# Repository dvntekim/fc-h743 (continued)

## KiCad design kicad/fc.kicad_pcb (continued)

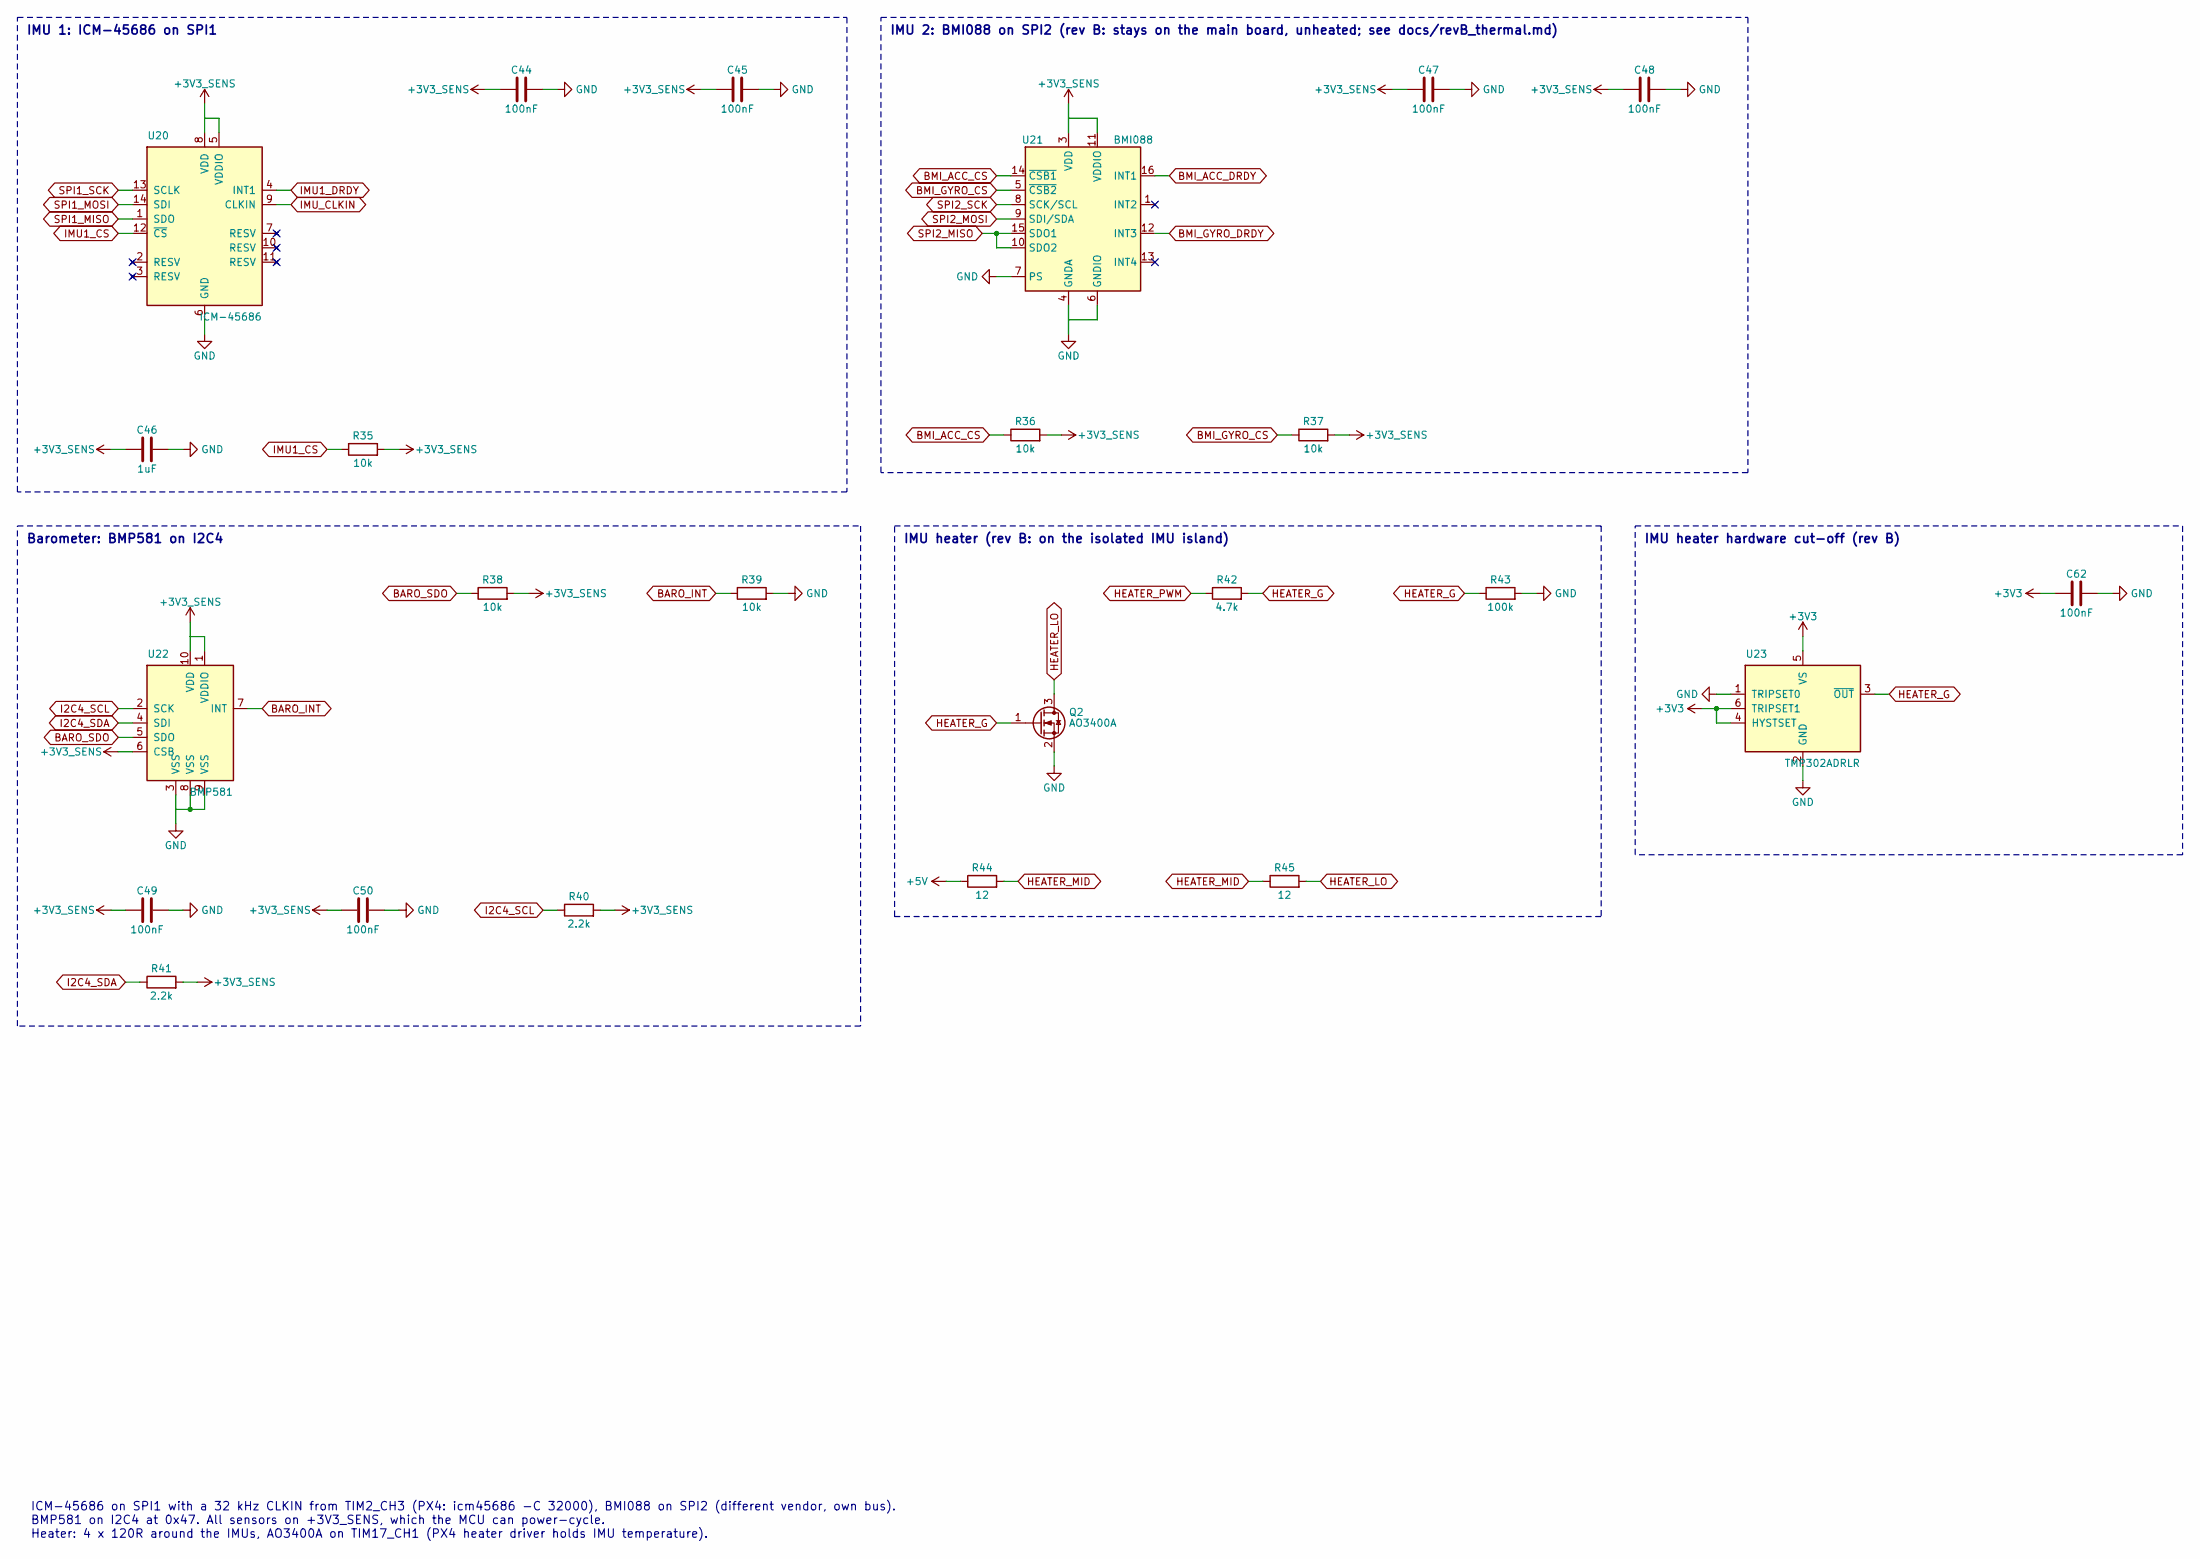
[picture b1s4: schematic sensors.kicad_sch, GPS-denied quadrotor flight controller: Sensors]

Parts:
C44, C45, C47, C48, C49, C50, C62: 100nF; C_0402_1005Metric; Rating 16V X7R; LCSC C1525
C46: 1uF; C_0402_1005Metric; Rating 25V X5R; LCSC C52923
Q2: AO3400A; SOT-23; LCSC C20917
R35, R36, R37, R38, R39: 10k; R_0402_1005Metric; LCSC C25744
R40, R41: 2.2k; R_0402_1005Metric; LCSC C25879
R42: 4.7k; R_0402_1005Metric; LCSC C25900
R43: 100k; R_0402_1005Metric; LCSC C25741
R44, R45: 12; R_2010_5025Metric; LCSC C3013299
U20: ICM-45686; LGA-14_3x2.5mm_P0.5mm_LayoutBorder3x4y; LCSC C22459454
U21: BMI088; Bosch_LGA-16_4.5x3mm_P0.5mm_LayoutBorder7x1y_ClockwisePinNu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; LCSC C194919
U22: BMP581; Bosch_LGA-10_2x2mm_P0.5mm_BMP581; LCSC C5362283
U23: TMP302ADRLR; SOT-563; LCSC C2877557

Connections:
+3V3: C62.1, U23.4 (HYSTSET), U23.5 (VS), U23.6 (TRIPSET1); also elsewhere on the board
+3V3_SENS: C44.1, C45.1, C46.1, C47.1, C48.1, C49.1, C50.1, R35.2, R36.2, R37.2, R38.2, R40.2, R41.2, U20.5 (VDDIO), U20.8 (VDD), U21.3 (VDD), U21.11 (VDDIO), U22.1 (VDDIO), U22.6 (CSB), U22.10 (VDD); also elsewhere on the board
+5V: R44.1; also elsewhere on the board
BARO_INT: R39.1, U22.7 (INT)
BARO_SDO: R38.1, U22.5 (SDO)
BMI_ACC_CS: R36.1, U21.14 (~CSB1); also elsewhere on the board
BMI_ACC_DRDY: U21.16 (INT1); also elsewhere on the board
BMI_GYRO_CS: R37.1, U21.5 (~CSB2); also elsewhere on the board
BMI_GYRO_DRDY: U21.12 (INT3); also elsewhere on the board
GND: C44.2, C45.2, C46.2, C47.2, C48.2, C49.2, C50.2, C62.2, Q2.2 (S), R39.2, R43.2, U20.6 (GND), U21.2 (GNDA), U21.4 (GNDA), U21.6 (GNDIO), U21.7 (PS), U22.3 (VSS), U22.8 (VSS), U22.9 (VSS), U23.1 (TRIPSET0), U23.2 (GND); also elsewhere on the board
HEATER_G: Q2.1 (G), R42.2, R43.1, U23.3 (~OUT)
HEATER_LO: Q2.3 (D), R45.2
HEATER_MID: R44.2, R45.1
HEATER_PWM: R42.1; also elsewhere on the board
I2C4_SCL: R40.1, U22.2 (SCK); also elsewhere on the board
I2C4_SDA: R41.1, U22.4 (SDI); also elsewhere on the board
IMU1_CS: R35.1, U20.12 (~CS); also elsewhere on the board
IMU1_DRDY: U20.4 (INT1); also elsewhere on the board
IMU_CLKIN: U20.9 (CLKIN); also elsewhere on the board
SPI1_MISO: U20.1 (SDO); also elsewhere on the board
SPI1_MOSI: U20.14 (SDI); also elsewhere on the board
SPI1_SCK: U20.13 (SCLK); also elsewhere on the board
SPI2_MISO: U21.10 (SDO2), U21.15 (SDO1); also elsewhere on the board
SPI2_MOSI: U21.9 (SDI/SDA); also elsewhere on the board
SPI2_SCK: U21.8 (SCK/SCL); also elsewhere on the board

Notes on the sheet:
IMU 1: ICM-45686 on SPI1
IMU 2: BMI088 on SPI2 (rev B: stays on the main board, unheated; see docs/revB_thermal.md)
Barometer: BMP581 on I2C4
IMU heater (rev B: on the isolated IMU island)
IMU heater hardware cut-off (rev B)
ICM-45686 on SPI1 with a 32 kHz CLKIN from TIM2_CH3 (PX4: icm45686 -C 32000), BMI088 on SPI2 (different vendor, own bus). BMP581 on I2C4 at 0x47. All sensors on +3V3_SENS, which the MCU can power-cycle. Heater: 4 x 120R around the IMUs, AO3400A on TIM17_CH1 (PX4 heater driver holds IMU temperature).

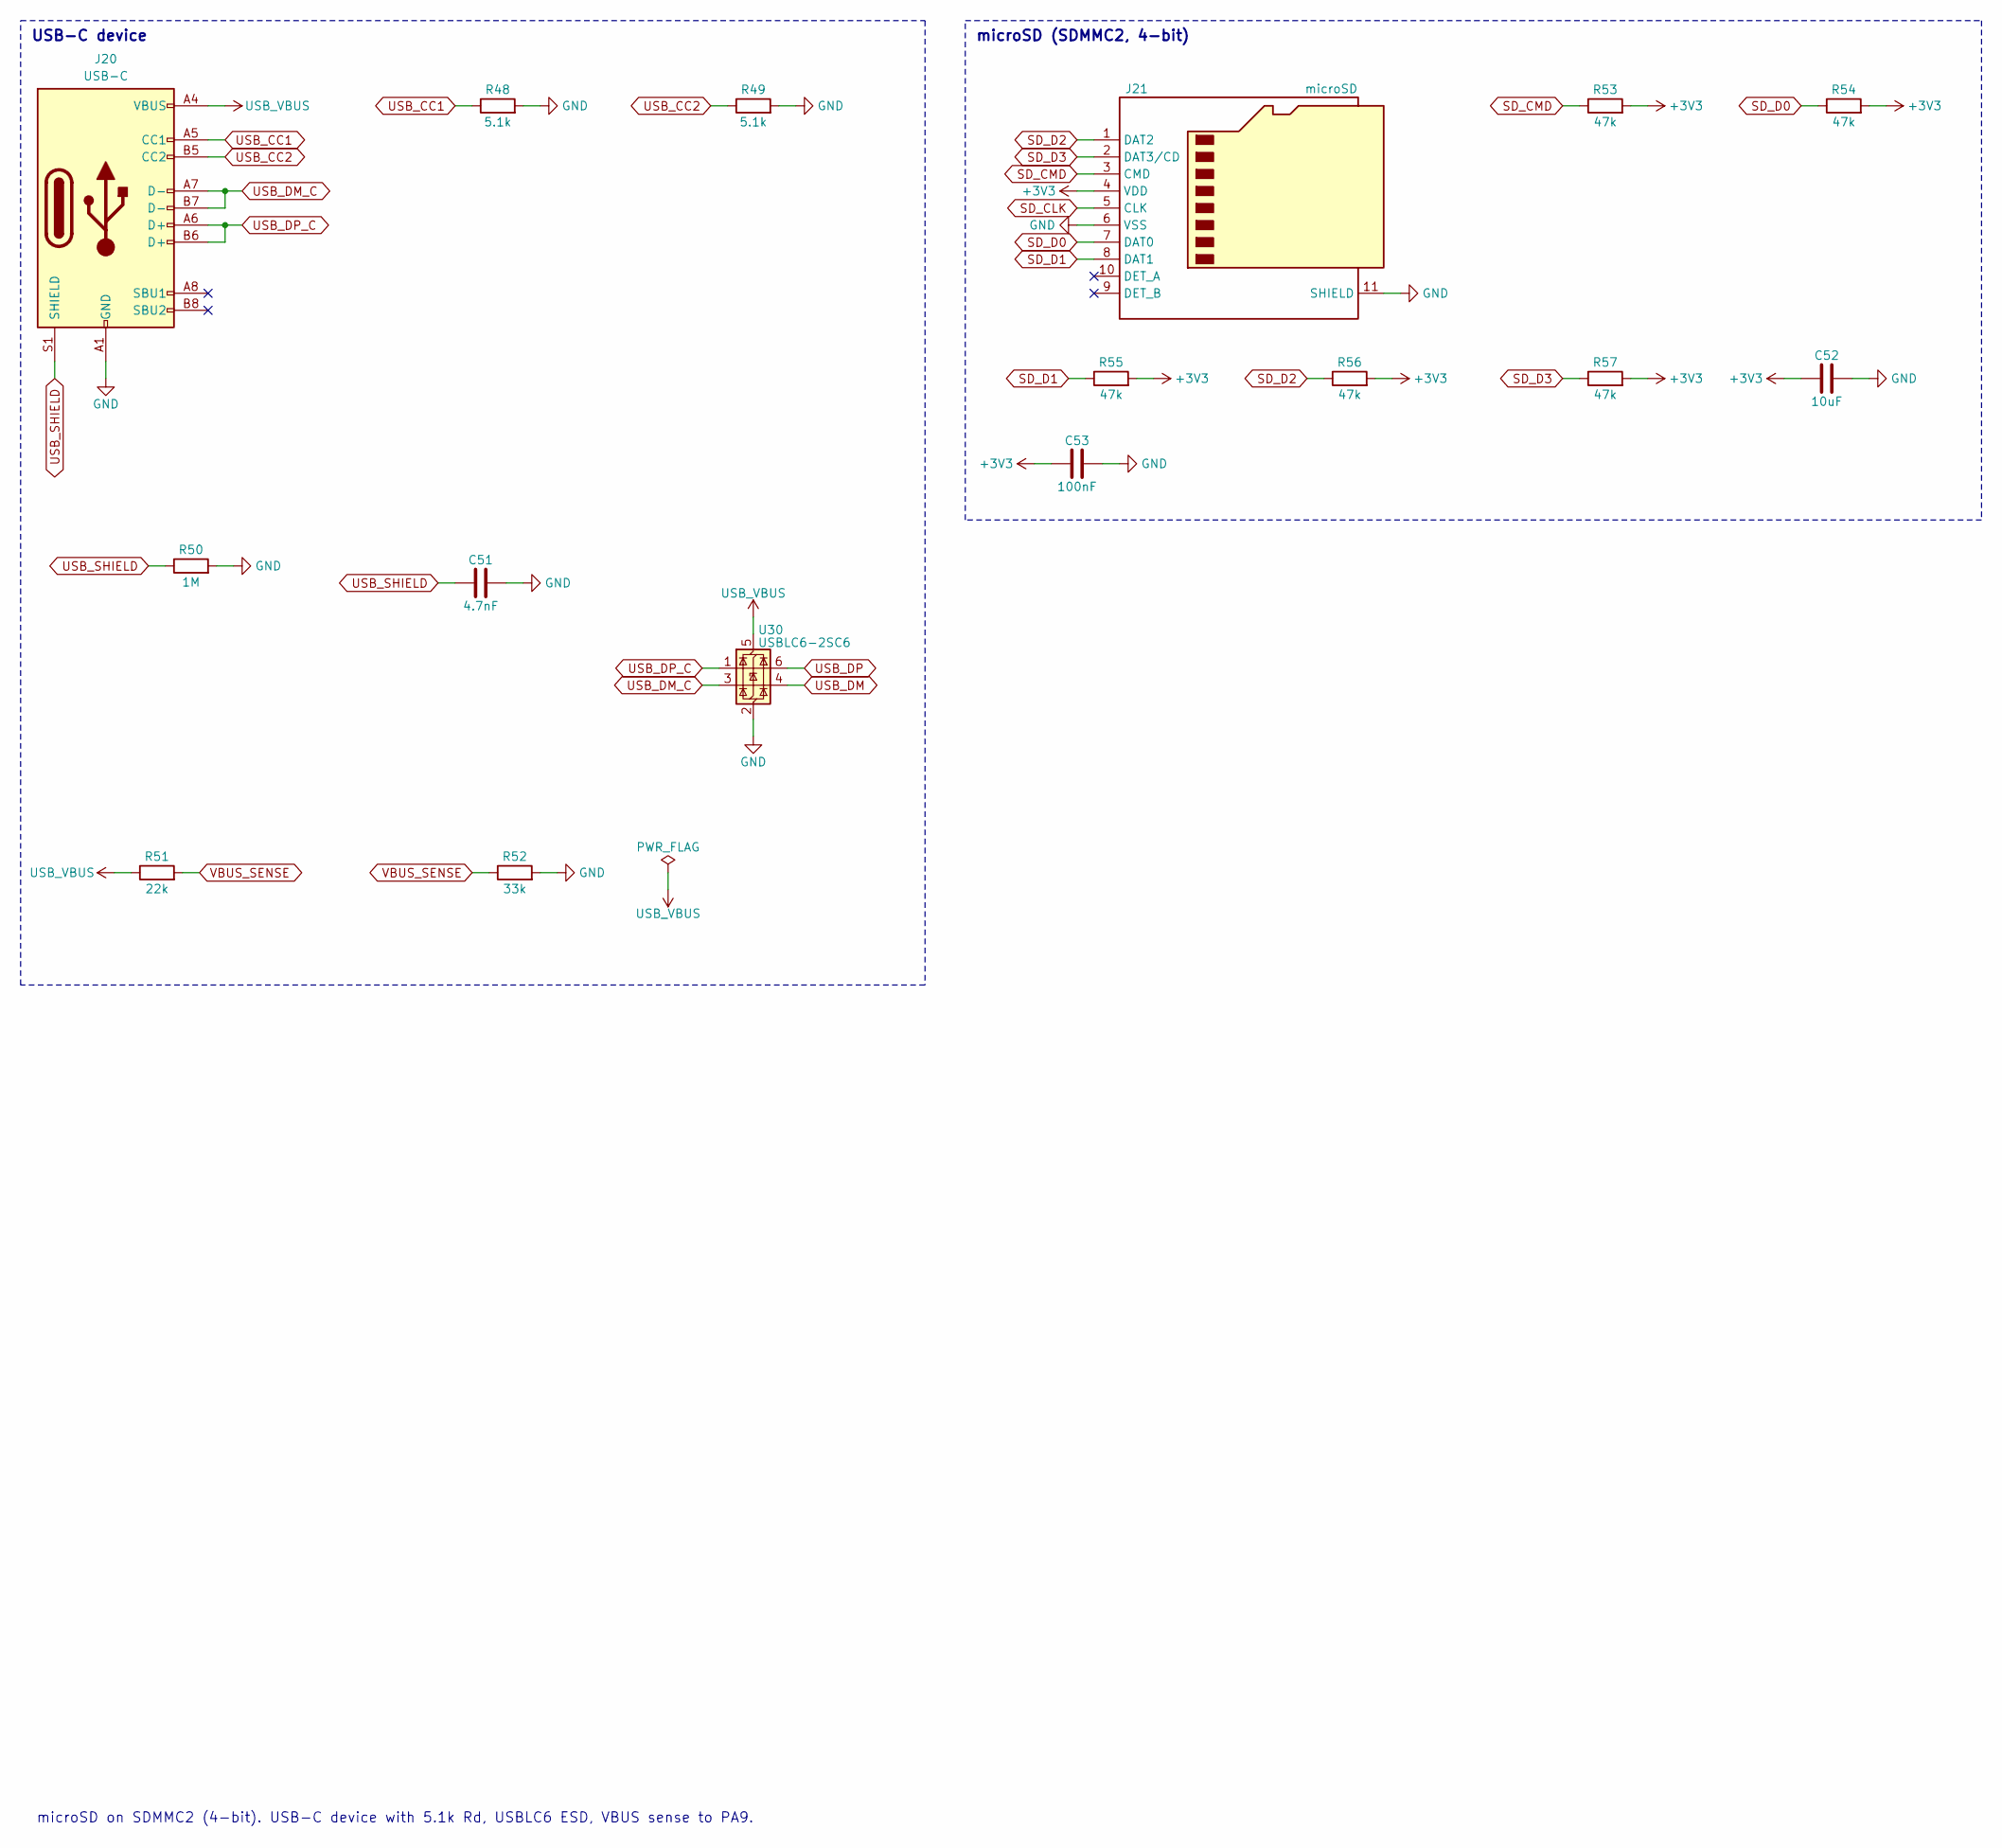
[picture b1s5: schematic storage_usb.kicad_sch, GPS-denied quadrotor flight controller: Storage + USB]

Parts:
C51: 4.7nF; C_0402_1005Metric; Rating 50V X7R; LCSC C1538
C52: 10uF; C_0603_1608Metric; Rating 10V X5R; LCSC C19702
C53: 100nF; C_0402_1005Metric; Rating 16V X7R; LCSC C1525
J20: USB-C; USB_C_Receptacle_HRO_TYPE-C-31-M-12; LCSC C165948
J21: microSD; microSD_HC_Hirose_DM3AT-SF-PEJM5; LCSC C114218
R48, R49: 5.1k; R_0402_1005Metric; LCSC C25905
R50: 1M; R_0402_1005Metric; LCSC C26083
R51: 22k; R_0402_1005Metric; LCSC C25768
R52: 33k; R_0402_1005Metric; LCSC C25779
R53, R54, R55, R56, R57: 47k; R_0402_1005Metric; LCSC C25792
U30: USBLC6-2SC6; SOT-23-6; LCSC C7519

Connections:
+3V3: C52.1, C53.1, J21.4 (VDD), R53.2, R54.2, R55.2, R56.2, R57.2; also elsewhere on the board
GND: C51.2, C52.2, C53.2, J20.A1 (GND), J20.A12 (GND), J20.B1 (GND), J20.B12 (GND), J21.6 (VSS), J21.11 (SHIELD), R48.2, R49.2, R50.2, R52.2, U30.2 (GND); also elsewhere on the board
SD_CLK: J21.5 (CLK); also elsewhere on the board
SD_CMD: J21.3 (CMD), R53.1; also elsewhere on the board
SD_D0: J21.7 (DAT0), R54.1; also elsewhere on the board
SD_D1: J21.8 (DAT1), R55.1; also elsewhere on the board
SD_D2: J21.1 (DAT2), R56.1; also elsewhere on the board
SD_D3: J21.2 (DAT3/CD), R57.1; also elsewhere on the board
USB_CC1: J20.A5 (CC1), R48.1
USB_CC2: J20.B5 (CC2), R49.1
USB_DM: U30.4 (I/O2); also elsewhere on the board
USB_DM_C: J20.A7 (D-), J20.B7 (D-), U30.3 (I/O2)
USB_DP: U30.6 (I/O1); also elsewhere on the board
USB_DP_C: J20.A6 (D+), J20.B6 (D+), U30.1 (I/O1)
USB_SHIELD: C51.1, J20.S1 (SHIELD), R50.1
USB_VBUS: J20.A4 (VBUS), J20.A9 (VBUS), J20.B4 (VBUS), J20.B9 (VBUS), R51.1, U30.5 (VBUS); also elsewhere on the board
VBUS_SENSE: R51.2, R52.1; also elsewhere on the board

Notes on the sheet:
USB-C device
microSD (SDMMC2, 4-bit)
microSD on SDMMC2 (4-bit). USB-C device with 5.1k Rd, USBLC6 ESD, VBUS sense to PA9.

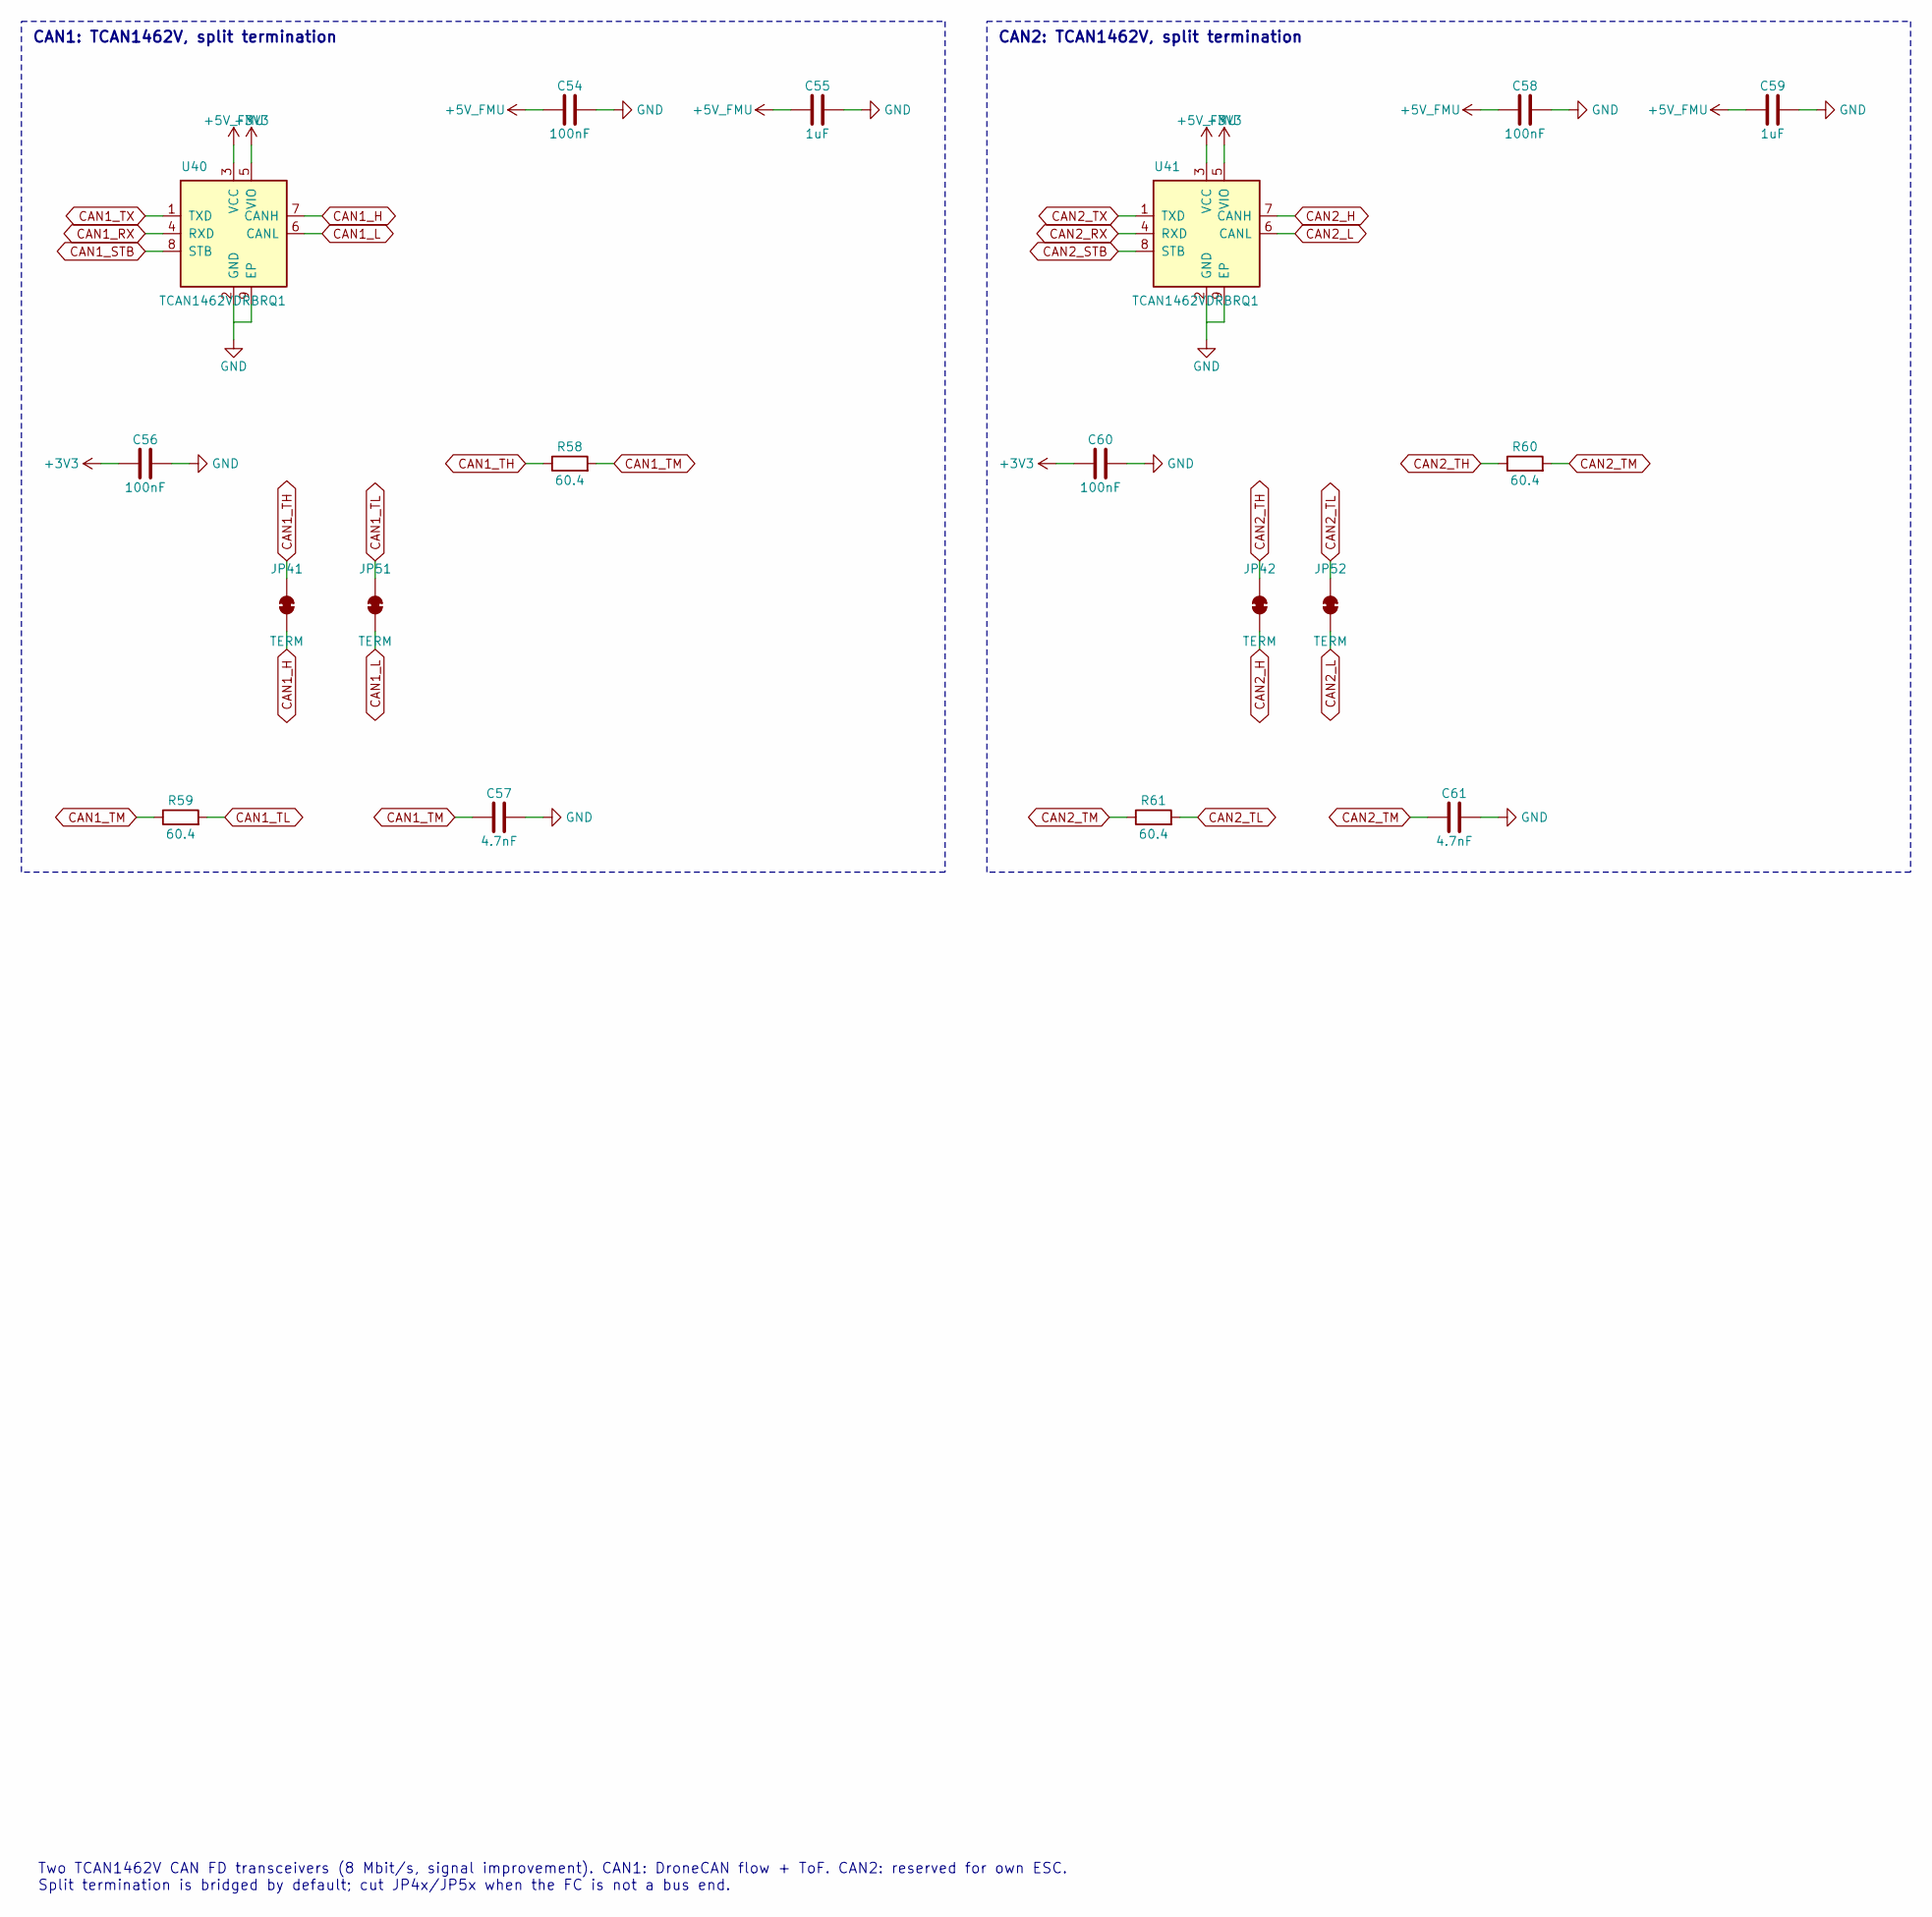
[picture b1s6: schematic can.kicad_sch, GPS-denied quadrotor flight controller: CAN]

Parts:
C54, C56, C58, C60: 100nF; C_0402_1005Metric; Rating 16V X7R; LCSC C1525
C55, C59: 1uF; C_0402_1005Metric; Rating 25V X5R; LCSC C52923
C57, C61: 4.7nF; C_0402_1005Metric; Rating 50V X7R; LCSC C1538
JP41, JP42, JP51, JP52: TERM; SolderJumper-2_P1.3mm_Bridged_RoundedPad1.0x1.5mm
R58, R59, R60, R61: 60.4; R_0402_1005Metric; LCSC C60310
U40, U41: TCAN1462VDRBRQ1; TI_DRB0008J_VSON-8_3x3mm_P0.65mm; LCSC C5215833

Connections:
+3V3: C56.1, C60.1, U40.5 (VIO), U41.5 (VIO); also elsewhere on the board
+5V_FMU: C54.1, C55.1, C58.1, C59.1, U40.3 (VCC), U41.3 (VCC); also elsewhere on the board
CAN1_H: JP41.1 (A), U40.7 (CANH); also elsewhere on the board
CAN1_L: JP51.1 (A), U40.6 (CANL); also elsewhere on the board
CAN1_RX: U40.4 (RXD); also elsewhere on the board
CAN1_STB: U40.8 (STB); also elsewhere on the board
CAN1_TH: JP41.2 (B), R58.1
CAN1_TL: JP51.2 (B), R59.2
CAN1_TM: C57.1, R58.2, R59.1
CAN1_TX: U40.1 (TXD); also elsewhere on the board
CAN2_H: JP42.1 (A), U41.7 (CANH); also elsewhere on the board
CAN2_L: JP52.1 (A), U41.6 (CANL); also elsewhere on the board
CAN2_RX: U41.4 (RXD); also elsewhere on the board
CAN2_STB: U41.8 (STB); also elsewhere on the board
CAN2_TH: JP42.2 (B), R60.1
CAN2_TL: JP52.2 (B), R61.2
CAN2_TM: C61.1, R60.2, R61.1
CAN2_TX: U41.1 (TXD); also elsewhere on the board
GND: C54.2, C55.2, C56.2, C57.2, C58.2, C59.2, C60.2, C61.2, U40.2 (GND), U40.9 (EP), U41.2 (GND), U41.9 (EP); also elsewhere on the board

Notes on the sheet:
CAN1: TCAN1462V, split termination
CAN2: TCAN1462V, split termination
Two TCAN1462V CAN FD transceivers (8 Mbit/s, signal improvement). CAN1: DroneCAN flow + ToF. CAN2: reserved for own ESC. Split termination is bridged by default; cut JP4x/JP5x when the FC is not a bus end.

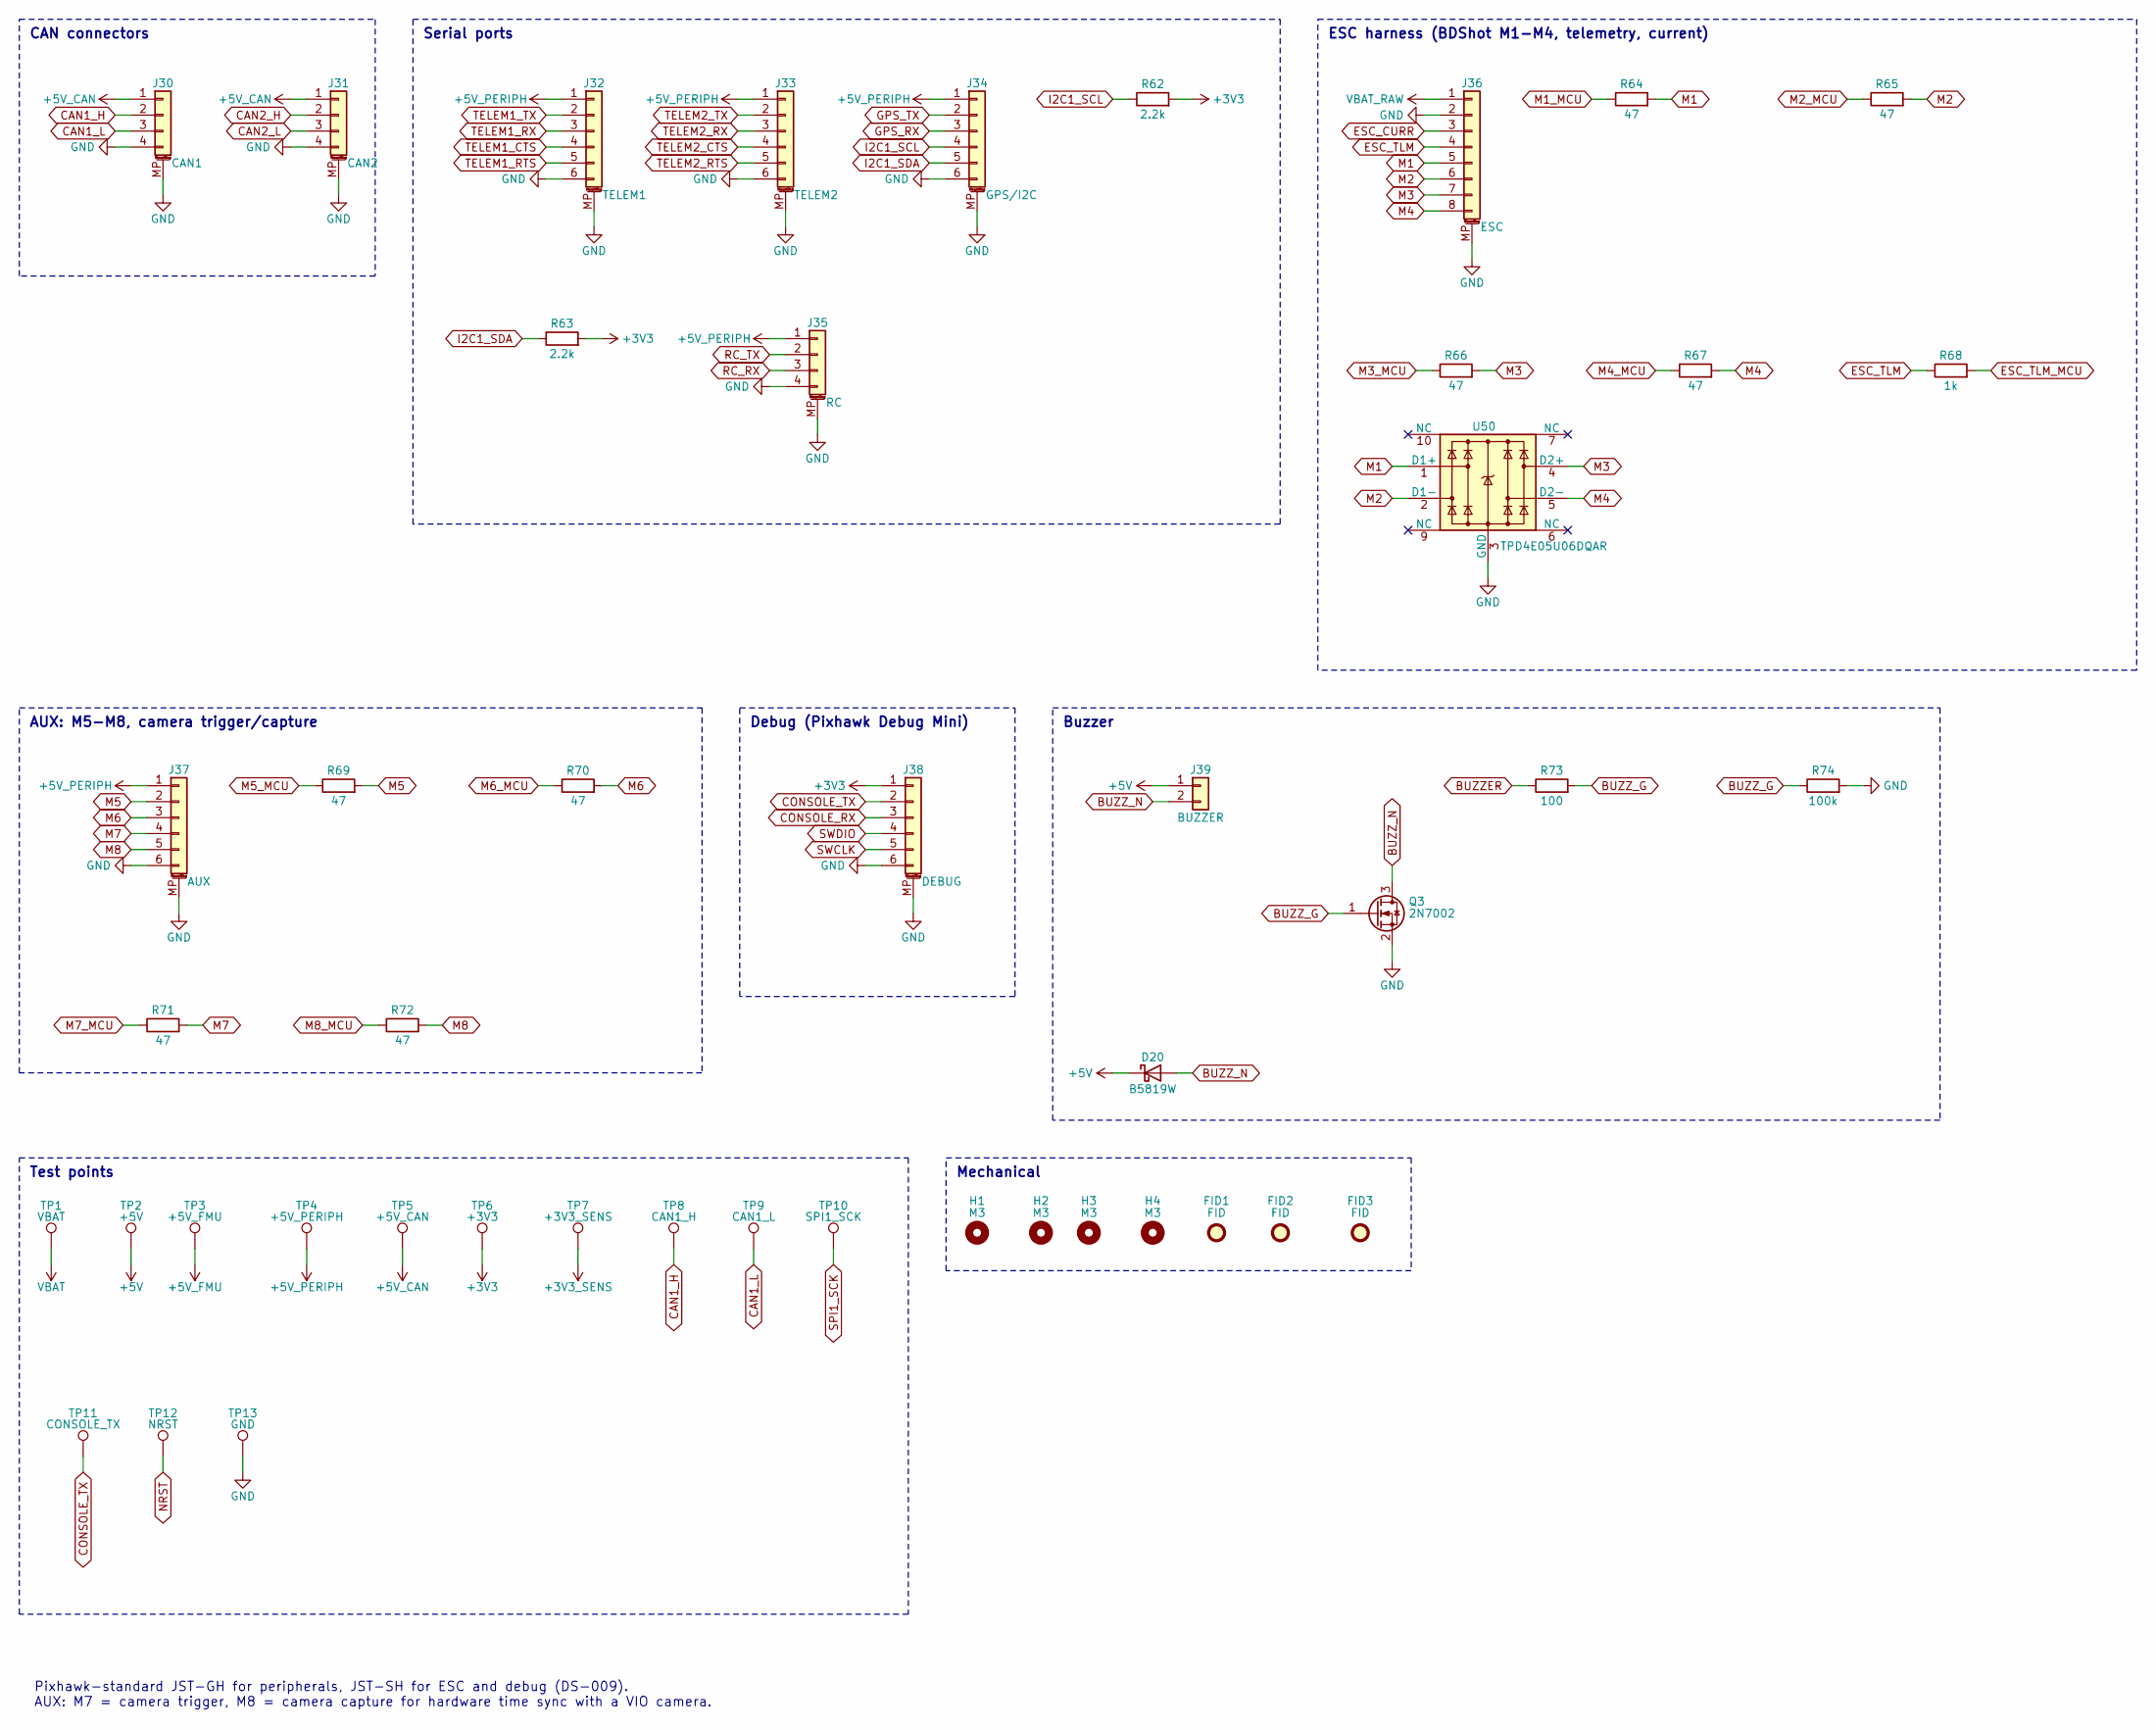
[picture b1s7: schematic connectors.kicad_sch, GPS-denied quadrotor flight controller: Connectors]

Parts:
D20: B5819W; D_SOD-123; LCSC C8598
FID1, FID2, FID3: FID; Fiducial_1mm_Mask2mm
H1, H2, H3, H4: M3; MountingHole_4.0mm_Grommet
J30: CAN1; JST_GH_SM04B-GHS-TB_1x04-1MP_P1.25mm_Horizontal; LCSC C189895
J31: CAN2; JST_GH_SM04B-GHS-TB_1x04-1MP_P1.25mm_Horizontal; LCSC C189895
J32: TELEM1; JST_GH_SM06B-GHS-TB_1x06-1MP_P1.25mm_Horizontal; LCSC C133065
J33: TELEM2; JST_GH_SM06B-GHS-TB_1x06-1MP_P1.25mm_Horizontal; LCSC C133065
J34: GPS/I2C; JST_GH_SM06B-GHS-TB_1x06-1MP_P1.25mm_Horizontal; LCSC C133065
J35: RC; JST_GH_SM04B-GHS-TB_1x04-1MP_P1.25mm_Horizontal; LCSC C189895
J36: ESC; JST_SH_SM08B-SRSS-TB_1x08-1MP_P1.00mm_Horizontal; LCSC C160407
J37: AUX; JST_SH_SM06B-SRSS-TB_1x06-1MP_P1.00mm_Horizontal; LCSC C56123098
J38: DEBUG; JST_SH_SM06B-SRSS-TB_1x06-1MP_P1.00mm_Horizontal; LCSC C56123098
J39: BUZZER; Pads_2x_1.5x2mm
Q3: 2N7002; SOT-23; LCSC C8545
R62, R63: 2.2k; R_0402_1005Metric; LCSC C25879
R64, R65, R66, R67, R69, R70, R71, R72: 47; R_0402_1005Metric; LCSC C25118
R68: 1k; R_0402_1005Metric; LCSC C11702
R73: 100; R_0402_1005Metric; LCSC C25076
R74: 100k; R_0402_1005Metric; LCSC C25741
TP1: VBAT; TestPoint_Pad_D1.0mm
TP2: +5V; TestPoint_Pad_D1.0mm
TP3: +5V_FMU; TestPoint_Pad_D1.0mm
TP4: +5V_PERIPH; TestPoint_Pad_D1.0mm
TP5: +5V_CAN; TestPoint_Pad_D1.0mm
TP6: +3V3; TestPoint_Pad_D1.0mm
TP7: +3V3_SENS; TestPoint_Pad_D1.0mm
TP8: CAN1_H; TestPoint_Pad_D1.0mm
TP9: CAN1_L; TestPoint_Pad_D1.0mm
TP10: SPI1_SCK; TestPoint_Pad_D1.0mm
TP11: CONSOLE_TX; TestPoint_Pad_D1.0mm
TP12: NRST; TestPoint_Pad_D1.0mm
TP13: GND; TestPoint_Pad_D1.0mm
U50: TPD4E05U06DQAR; USON-10_2.5x1.0mm_P0.5mm; LCSC C138714

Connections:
+3V3: J38.1, R62.2, R63.2, TP6.1; also elsewhere on the board
+3V3_SENS: TP7.1; also elsewhere on the board
+5V: D20.1 (K), J39.1, TP2.1; also elsewhere on the board
+5V_CAN: J30.1, J31.1, TP5.1; also elsewhere on the board
+5V_FMU: TP3.1; also elsewhere on the board
+5V_PERIPH: J32.1, J33.1, J34.1, J35.1, J37.1, TP4.1; also elsewhere on the board
BUZZER: R73.1; also elsewhere on the board
BUZZ_G: Q3.1 (G), R73.2, R74.1
BUZZ_N: D20.2 (A), J39.2, Q3.3 (D)
CAN1_H: J30.2, TP8.1; also elsewhere on the board
CAN1_L: J30.3, TP9.1; also elsewhere on the board
CAN2_H: J31.2; also elsewhere on the board
CAN2_L: J31.3; also elsewhere on the board
CONSOLE_RX: J38.3; also elsewhere on the board
CONSOLE_TX: J38.2, TP11.1; also elsewhere on the board
ESC_CURR: J36.3; also elsewhere on the board
ESC_TLM: J36.4, R68.1
ESC_TLM_MCU: R68.2; also elsewhere on the board
GND: J30.4, J30.MP (MountPin), J31.4, J31.MP (MountPin), J32.6, J32.MP (MountPin), J33.6, J33.MP (MountPin), J34.6, J34.MP (MountPin), J35.4, J35.MP (MountPin), J36.2, J36.MP (MountPin), J37.6, J37.MP (MountPin), J38.6, J38.MP (MountPin), Q3.2 (S), R74.2, TP13.1, U50.3 (GND), U50.8 (GND); also elsewhere on the board
GPS_RX: J34.3; also elsewhere on the board
GPS_TX: J34.2; also elsewhere on the board
I2C1_SCL: J34.4, R62.1; also elsewhere on the board
I2C1_SDA: J34.5, R63.1; also elsewhere on the board
M1: J36.5, R64.2, U50.1 (D1+)
M1_MCU: R64.1; also elsewhere on the board
M2: J36.6, R65.2, U50.2 (D1-)
M2_MCU: R65.1; also elsewhere on the board
M3: J36.7, R66.2, U50.4 (D2+)
M3_MCU: R66.1; also elsewhere on the board
M4: J36.8, R67.2, U50.5 (D2-)
M4_MCU: R67.1; also elsewhere on the board
M5: J37.2, R69.2
M5_MCU: R69.1; also elsewhere on the board
M6: J37.3, R70.2
M6_MCU: R70.1; also elsewhere on the board
M7: J37.4, R71.2
M7_MCU: R71.1; also elsewhere on the board
M8: J37.5, R72.2
M8_MCU: R72.1; also elsewhere on the board
NRST: TP12.1; also elsewhere on the board
RC_RX: J35.3; also elsewhere on the board
RC_TX: J35.2; also elsewhere on the board
SPI1_SCK: TP10.1; also elsewhere on the board
SWCLK: J38.5; also elsewhere on the board
SWDIO: J38.4; also elsewhere on the board
TELEM1_CTS: J32.4; also elsewhere on the board
TELEM1_RTS: J32.5; also elsewhere on the board
TELEM1_RX: J32.3; also elsewhere on the board
TELEM1_TX: J32.2; also elsewhere on the board
TELEM2_CTS: J33.4; also elsewhere on the board
TELEM2_RTS: J33.5; also elsewhere on the board
TELEM2_RX: J33.3; also elsewhere on the board
TELEM2_TX: J33.2; also elsewhere on the board
VBAT: TP1.1; also elsewhere on the board
VBAT_RAW: J36.1; also elsewhere on the board

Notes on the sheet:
CAN connectors
Serial ports
ESC harness (BDShot M1-M4, telemetry, current)
AUX: M5-M8, camera trigger/capture
Debug (Pixhawk Debug Mini)
Buzzer
Test points
Mechanical
Pixhawk-standard JST-GH for peripherals, JST-SH for ESC and debug (DS-009). AUX: M7 = camera trigger, M8 = camera capture for hardware time sync with a VIO camera.
